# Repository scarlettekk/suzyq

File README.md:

This breakout board should turn two regular USB c cables into a SuzyQ cable for Chromebook debugging. It hasn't been tested yet.

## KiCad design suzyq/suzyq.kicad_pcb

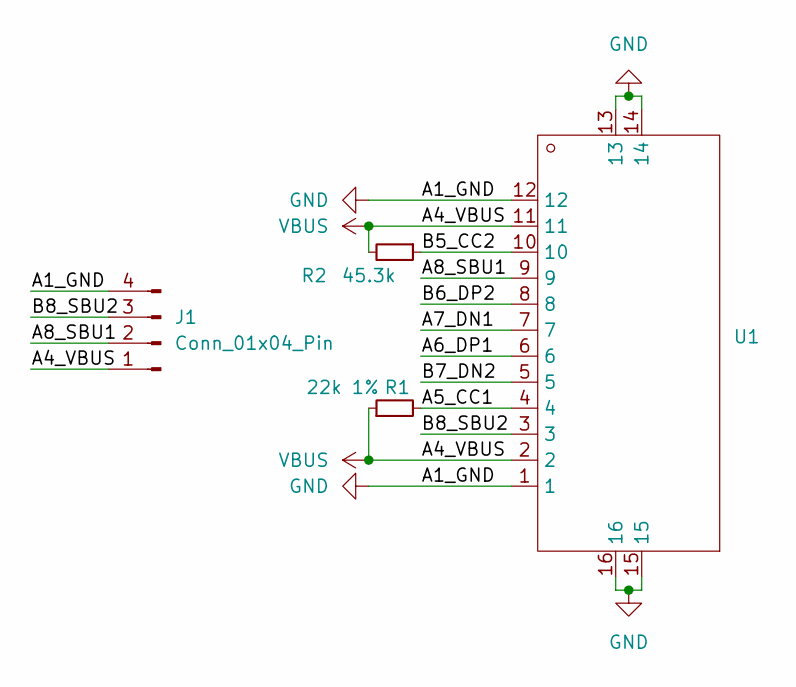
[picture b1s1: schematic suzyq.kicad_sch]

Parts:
J1: Conn_01x04_Pin; PinHeader_1x04_P2.54mm_Vertical
R1: 22k 1%; R_0402_1005Metric
R2: 45.3k; R_0402_1005Metric
U1: U262-161N-4BS165; Manufacturer Part U262-161N-4BS165; LCSC Part Name Type-C 母 卧贴

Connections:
/A5_CC1: R1.2, U1.4
/A6_DP1: U1.6
/A7_DN1: U1.7
/A8_SBU1: J1.2, U1.9
/B5_CC2: R2.1, U1.10
/B6_DP2: U1.8
/B7_DN2: U1.5
/B8_SBU2: J1.3, U1.3
GND: J1.4, U1.1, U1.12, U1.13, U1.14, U1.15, U1.16
VBUS: J1.1, R1.1, R2.2, U1.2, U1.11

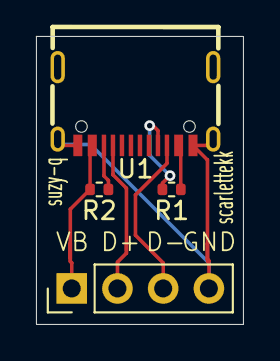
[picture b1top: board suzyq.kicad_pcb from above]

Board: 2 copper layers, 11.5 x 16.0 mm, 4 parts (0 on the bottom side), 6 nets.

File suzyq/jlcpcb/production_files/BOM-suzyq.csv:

Comment,Designator,Footprint,LCSC
Conn_01x04_Pin,J1,PinHeader_1x04_P2.54mm_Vertical,
45.3k,R2,R_0402_1005Metric,
~,U1,U262-161N-4BS165,
22k 1%,R1,R_0402_1005Metric,

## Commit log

2024-08-12 version 1
